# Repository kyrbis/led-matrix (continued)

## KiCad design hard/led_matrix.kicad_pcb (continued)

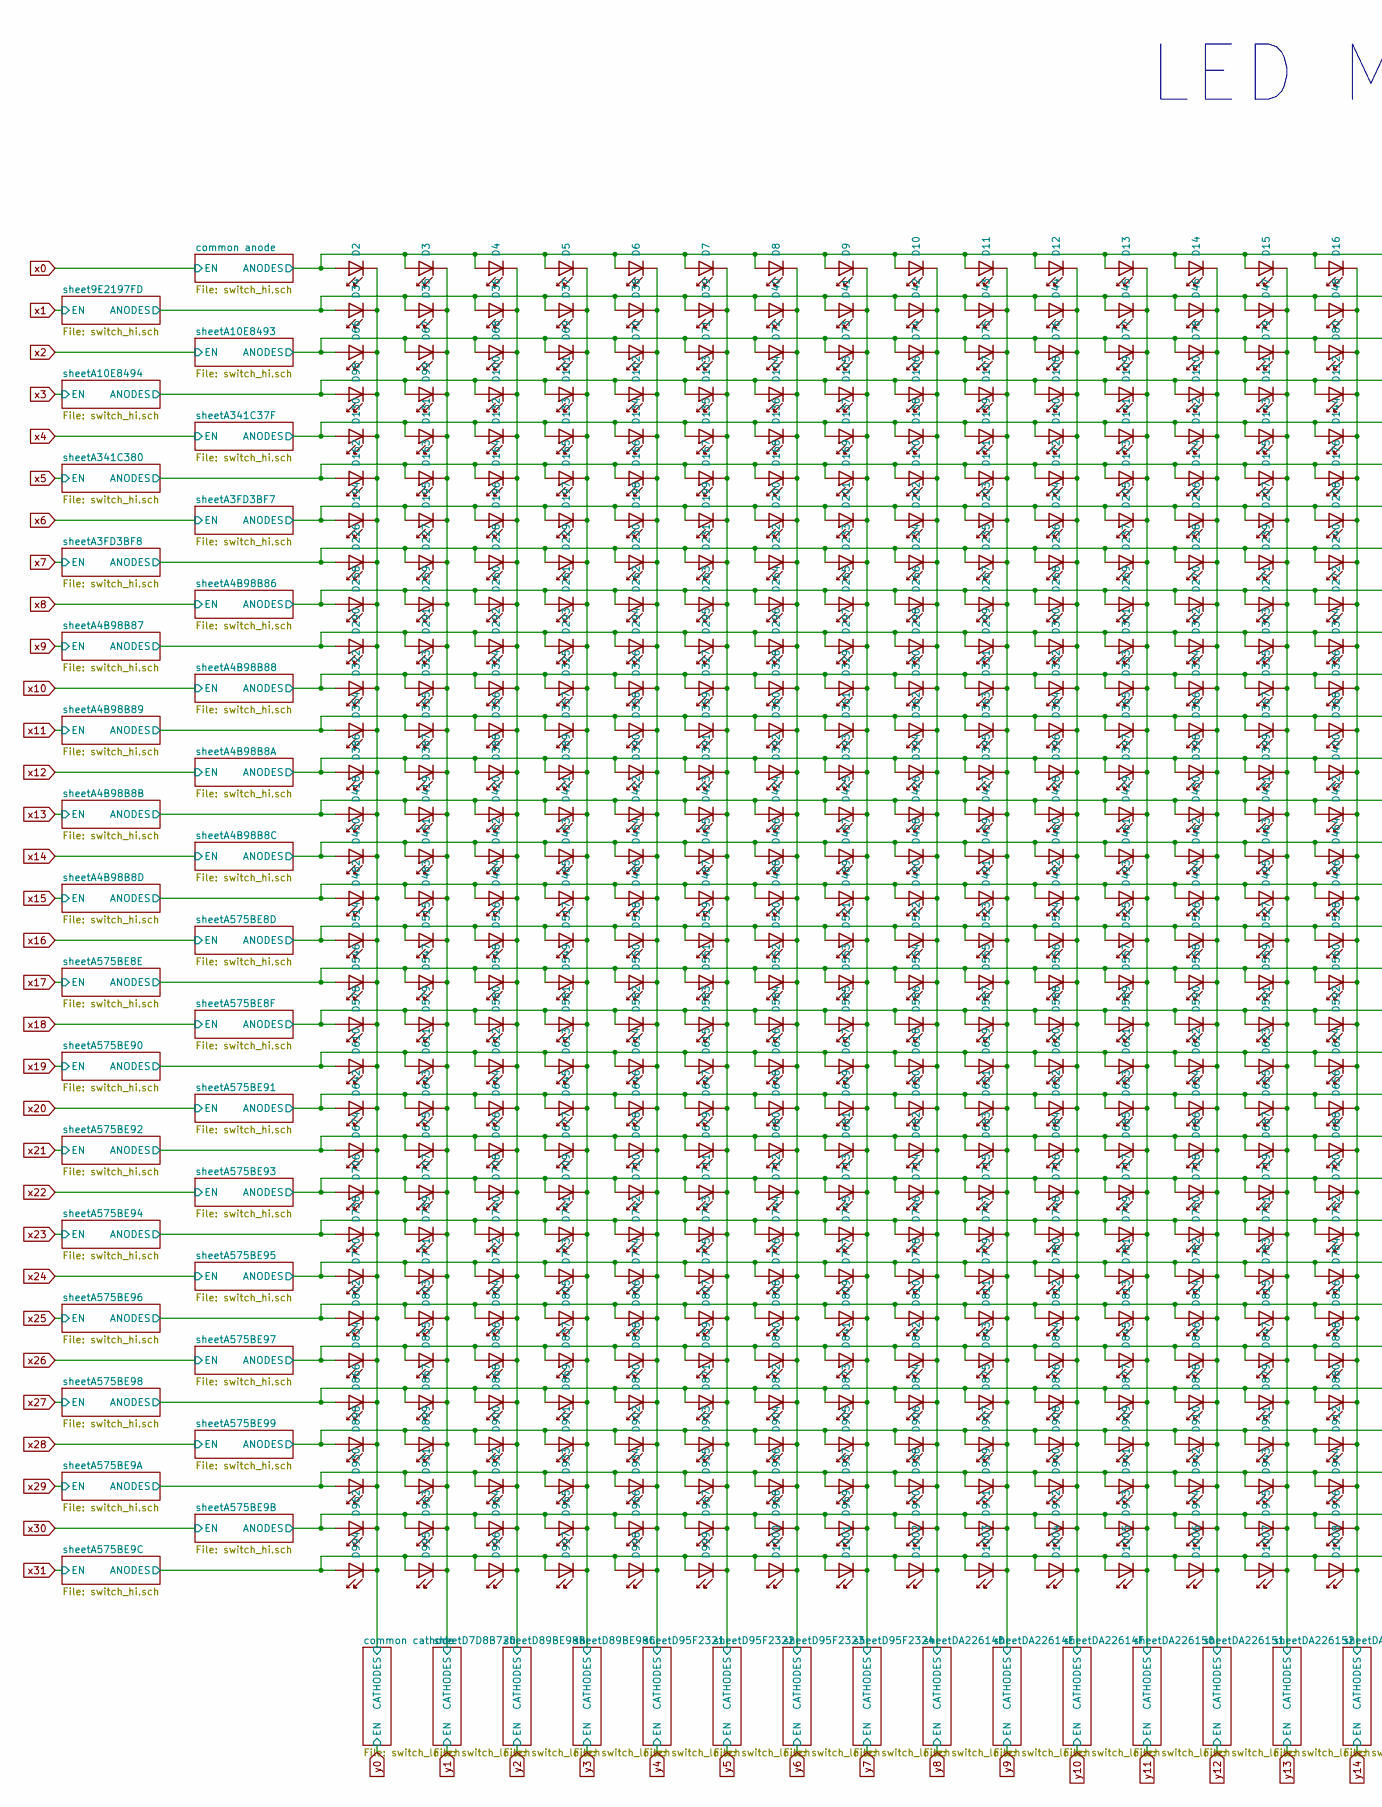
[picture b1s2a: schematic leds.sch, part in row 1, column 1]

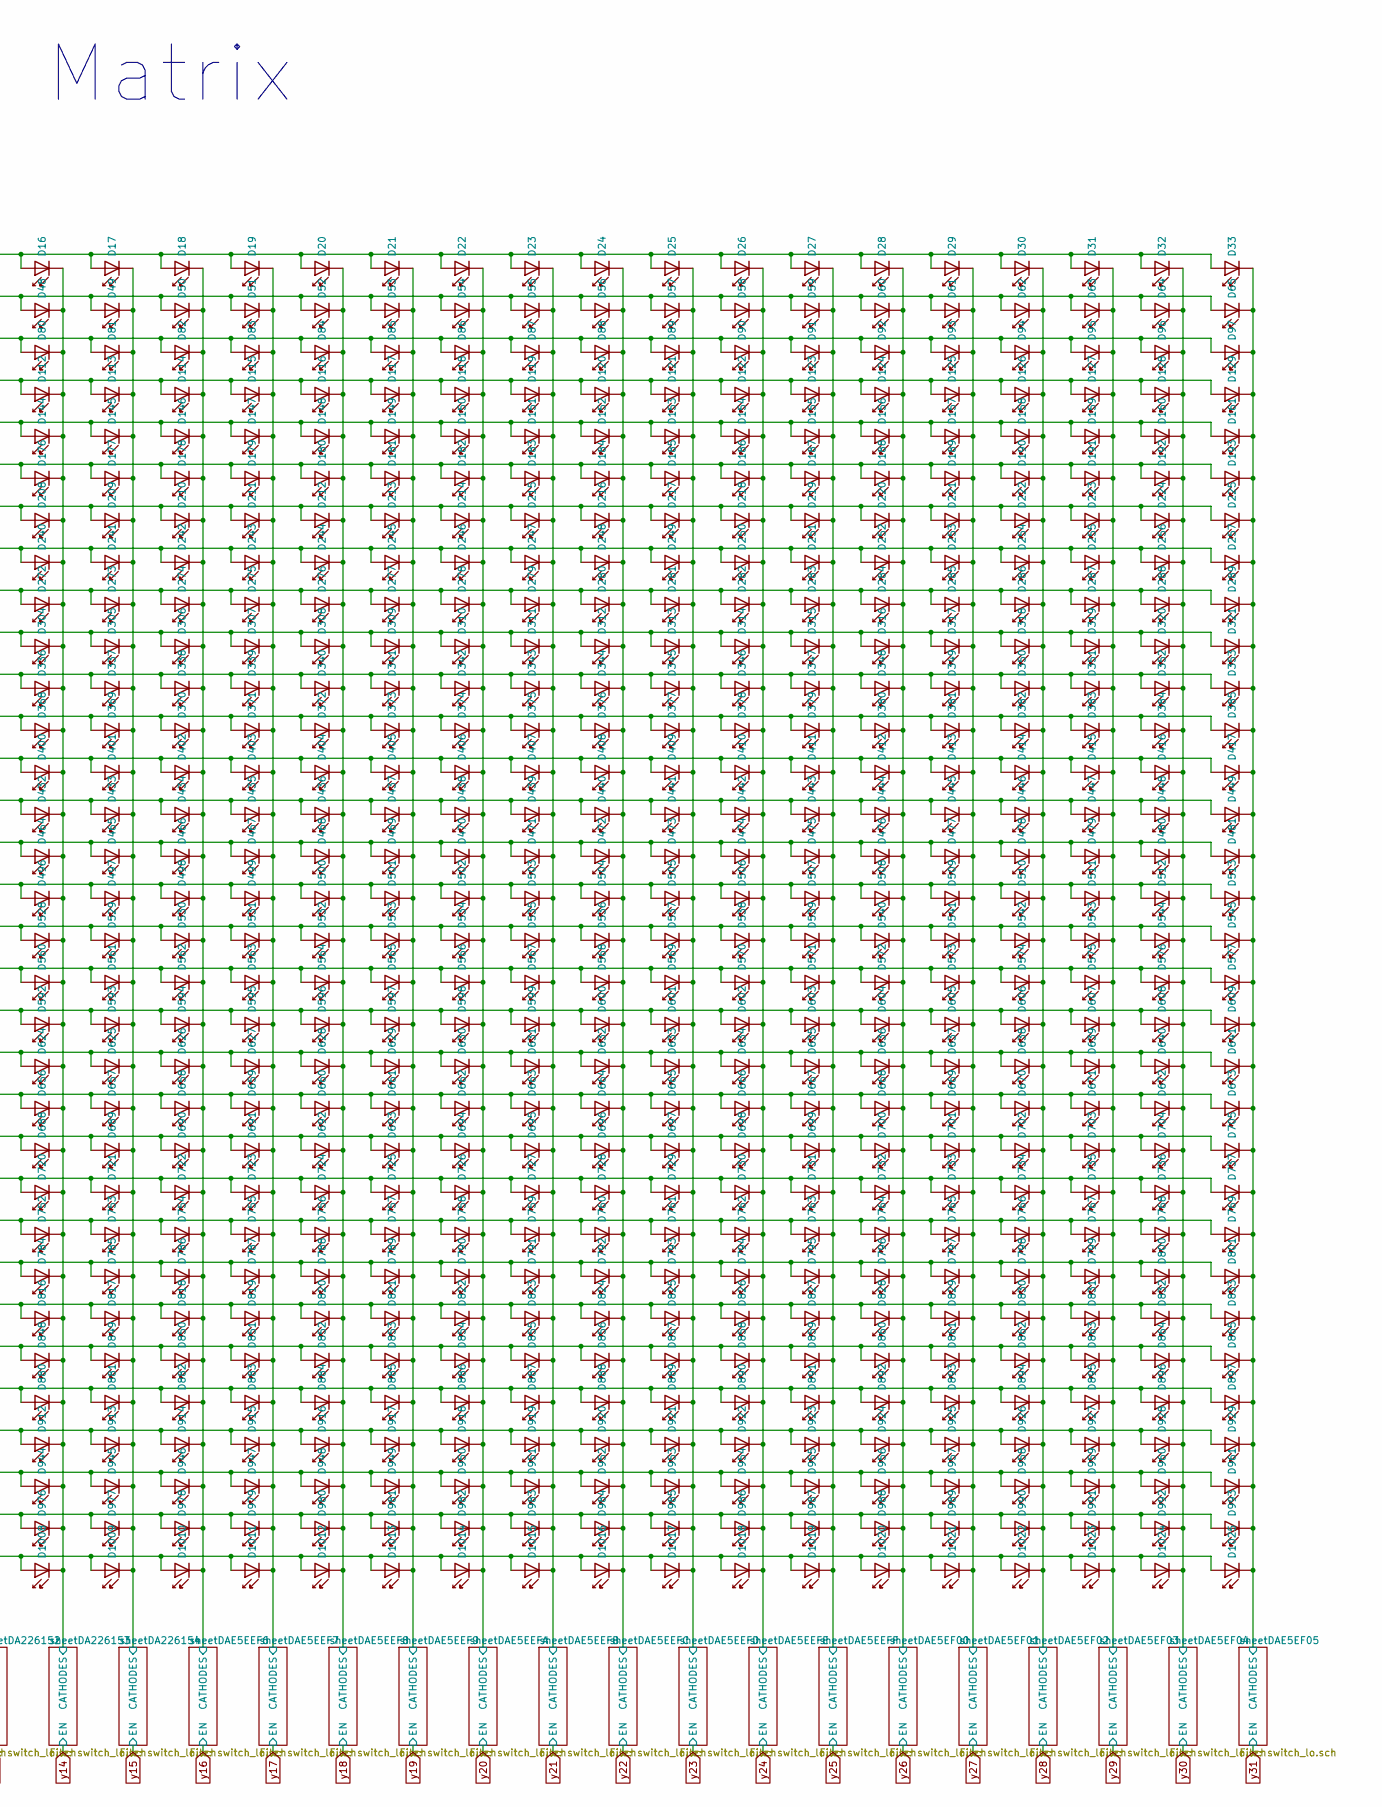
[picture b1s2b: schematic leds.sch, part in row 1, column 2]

Parts:
D2, D3, D4, D5, D6, D7, D8, D9, D10, D11, D12, D13, D14, D15, D16, D17, D18, D19, D20, D21, D22, D23, D24, D25, D26, D27, D28, D29, D30, D31, D32, D33, D34, D35, D36, D37, D38, D39, D40, D41, D42, D43, D44, D45, D46, D47, D48, D49, D50, D51, D52, D53, D54, D55, D56, D57, D58, D59, D60, D61, D62, D63, D64, D65, D66, D67, D68, D69, D70, D71, D72, D73, D74, D75, D76, D77, D78, D79, D80, D81, D82, D83, D84, D85, D86, D87, D88, D89, D90, D91, D92, D93, D94, D95, D96, D97, D98, D99, D100, D101, D102, D103, D104, D105, D106, D107, D108, D109, D110, D111, D112, D113, D114, D115, D116, D117, D118, D119, D120, D121, D122, D123, D124, D125, D126, D127, D128, D129, D130, D131, D132, D133, D134, D135, D136, D137, D138, D139, D140, D141, D142, D143, D144, D145, D146, D147, D148, D149, D150, D151, D152, D153, D154, D155, D156, D157, D158, D159, D160, D161, D162, D163, D164, D165, D166, D167, D168, D169, D170, D171, D172, D173, D174, D175, D176, D177, D178, D179, D180, D181, D182, D183, D184, D185, D186, D187, D188, D189, D190, D191, D192, D193, D194, D195, D196, D197, D198, D199, D200, D201, D202, D203, D204, D205, D206, D207, D208, D209, D210, D211, D212, D213, D214, D215, D216, D217, D218, D219, D220, D221, D222, D223, D224, D225, D226, D227, D228, D229, D230, D231, D232, D233, D234, D235, D236, D237, D238, D239, D240, D241, D242, D243, D244, D245, D246, D247, D248, D249, D250, D251, D252, D253, D254, D255, D256, D257, D258, D259, D260, D261, D262, D263, D264, D265, D266, D267, D268, D269, D270, D271, D272, D273, D274, D275, D276, D277, D278, D279, D280, D281, D282, D283, D284, D285, D286, D287, D288, D289, D290, D291, D292, D293, D294, D295, D296, D297, D298, D299, D300, D301, D302, D303, D304, D305, D306, D307, D308, D309, D310, D311, D312, D313, D314, D315, D316, D317, D318, D319, D320, D321, D322, D323, D324, D325, D326, D327, D328, D329, D330, D331, D332, D333, D334, D335, D336, D337, D338, D339, D340, D341, D342, D343, D344, D345, D346, D347, D348, D349, D350, D351, D352, D353, D354, D355, D356, D357, D358, D359, D360, D361, D362, D363, D364, D365, D366, D367, D368, D369, D370, D371, D372, D373, D374, D375, D376, D377, D378, D379, D380, D381, D382, D383, D384, D385, D386, D387, D388, D389, D390, D391, D392, D393, D394, D395, D396, D397, D398, D399, D400, D401, D402, D403, D404, D405, D406, D407, D408, D409, D410, D411, D412, D413, D414, D415, D416, D417, D418, D419, D420, D421, D422, D423, D424, D425, D426, D427, D428, D429, D430, D431, D432, D433, D434, D435, D436, D437, D438, D439, D440, D441, D442, D443, D444, D445, D446, D447, D448, D449, D450, D451, D452, D453, D454, D455, D456, D457, D458, D459, D460, D461, D462, D463, D464, D465, D466, D467, D468, D469, D470, D471, D472, D473, D474, D475, D476, D477, D478, D479, D480, D481, D482, D483, D484, D485, D486, D487, D488, D489, D490, D491, D492, D493, D494, D495, D496, D497, D498, D499, D500, D501, D502, D503, D504, D505, D506, D507, D508, D509, D510, D511, D512, D513, D514, D515, D516, D517, D518, D519, D520, D521, D522, D523, D524, D525, D526, D527, D528, D529, D530, D531, D532, D533, D534, D535, D536, D537, D538, D539, D540, D541, D542, D543, D544, D545, D546, D547, D548, D549, D550, D551, D552, D553, D554, D555, D556, D557, D558, D559, D560, D561, D562, D563, D564, D565, D566, D567, D568, D569, D570, D571, D572, D573, D574, D575, D576, D577, D578, D579, D580, D581, D582, D583, D584, D585, D586, D587, D588, D589, D590, D591, D592, D593, D594, D595, D596, D597, D598, D599, D600, D601, D602, D603, D604, D605, D606, D607, D608, D609, D610, D611, D612, D613, D614, D615, D616, D617, D618, D619, D620, D621, D622, D623, D624, D625, D626, D627, D628, D629, D630, D631, D632, D633, D634, D635, D636, D637, D638, D639, D640, D641, D642, D643, D644, D645, D646, D647, D648, D649, D650, D651, D652, D653, D654, D655, D656, D657, D658, D659, D660, D661, D662, D663, D664, D665, D666, D667, D668, D669, D670, D671, D672, D673, D674, D675, D676, D677, D678, D679, D680, D681, D682, D683, D684, D685, D686, D687, D688, D689, D690, D691, D692, D693, D694, D695, D696, D697, D698, D699, D700, D701, D702, D703, D704, D705, D706, D707, D708, D709, D710, D711, D712, D713, D714, D715, D716, D717, D718, D719, D720, D721, D722, D723, D724, D725, D726, D727, D728, D729, D730, D731, D732, D733, D734, D735, D736, D737, D738, D739, D740, D741, D742, D743, D744, D745, D746, D747, D748, D749, D750, D751, D752, D753, D754, D755, D756, D757, D758, D759, D760, D761, D762, D763, D764, D765, D766, D767, D768, D769, D770, D771, D772, D773, D774, D775, D776, D777, D778, D779, D780, D781, D782, D783, D784, D785, D786, D787, D788, D789, D790, D791, D792, D793, D794, D795, D796, D797, D798, D799, D800, D801, D802, D803, D804, D805, D806, D807, D808, D809, D810, D811, D812, D813, D814, D815, D816, D817, D818, D819, D820, D821, D822, D823, D824, D825, D826, D827, D828, D829, D830, D831, D832, D833, D834, D835, D836, D837, D838, D839, D840, D841, D842, D843, D844, D845, D846, D847, D848, D849, D850, D851, D852, D853, D854, D855, D856, D857, D858, D859, D860, D861, D862, D863, D864, D865, D866, D867, D868, D869, D870, D871, D872, D873, D874, D875, D876, D877, D878, D879, D880, D881, D882, D883, D884, D885, D886, D887, D888, D889, D890, D891, D892, D893, D894, D895, D896, D897, D898, D899, D900, D901, D902, D903, D904, D905, D906, D907, D908, D909, D910, D911, D912, D913, D914, D915, D916, D917, D918, D919, D920, D921, D922, D923, D924, D925, D926, D927, D928, D929, D930, D931, D932, D933, D934, D935, D936, D937, D938, D939, D940, D941, D942, D943, D944, D945, D946, D947, D948, D949, D950, D951, D952, D953, D954, D955, D956, D957, D958, D959, D960, D961, D962, D963, D964, D965, D966, D967, D968, D969, D970, D971, D972, D973, D974, D975, D976, D977, D978, D979, D980, D981, D982, D983, D984, D985, D986, D987, D988, D989, D990, D991, D992, D993, D994, D995, D996, D997, D998, D999, D1000, D1001, D1002, D1003, D1004, D1005, D1006, D1007, D1008, D1009, D1010, D1011, D1012, D1013, D1014, D1015, D1016, D1017, D1018, D1019, D1020, D1021, D1022, D1023, D1024, D1025: LTST-S270TBKT; LED_LiteOn_LTST-S270TBKT; Mouser_Part_Number 859-LTST-S270TBKT; DigiKey_Part_Number LTST-S270TBKT-5A-ND

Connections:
/led matrix/common anode/ANODES: D2.A, D3.A, D4.A, D5.A, D6.A, D7.A, D8.A, D9.A, D10.A, D11.A, D12.A, D13.A, D14.A, D15.A, D16.A, D17.A, D18.A, D19.A, D20.A, D21.A, D22.A, D23.A, D24.A, D25.A, D26.A, D27.A, D28.A, D29.A, D30.A, D31.A, D32.A, D33.A; also elsewhere on the board
/led matrix/common cathode/CATHODES: D2.C, D34.C, D66.C, D98.C, D130.C, D162.C, D194.C, D226.C, D258.C, D290.C, D322.C, D354.C, D386.C, D418.C, D450.C, D482.C, D514.C, D546.C, D578.C, D610.C, D642.C, D674.C, D706.C, D738.C, D770.C, D802.C, D834.C, D866.C, D898.C, D930.C, D962.C, D994.C; also elsewhere on the board
/led matrix/sheet9E2197FD/ANODES: D34.A, D35.A, D36.A, D37.A, D38.A, D39.A, D40.A, D41.A, D42.A, D43.A, D44.A, D45.A, D46.A, D47.A, D48.A, D49.A, D50.A, D51.A, D52.A, D53.A, D54.A, D55.A, D56.A, D57.A, D58.A, D59.A, D60.A, D61.A, D62.A, D63.A, D64.A, D65.A; also elsewhere on the board
/led matrix/sheetA3FD3BF7/ANODES: D194.A, D195.A, D196.A, D197.A, D198.A, D199.A, D200.A, D201.A, D202.A, D203.A, D204.A, D205.A, D206.A, D207.A, D208.A, D209.A, D210.A, D211.A, D212.A, D213.A, D214.A, D215.A, D216.A, D217.A, D218.A, D219.A, D220.A, D221.A, D222.A, D223.A, D224.A, D225.A; also elsewhere on the board
/led matrix/sheetA3FD3BF8/ANODES: D226.A, D227.A, D228.A, D229.A, D230.A, D231.A, D232.A, D233.A, D234.A, D235.A, D236.A, D237.A, D238.A, D239.A, D240.A, D241.A, D242.A, D243.A, D244.A, D245.A, D246.A, D247.A, D248.A, D249.A, D250.A, D251.A, D252.A, D253.A, D254.A, D255.A, D256.A, D257.A; also elsewhere on the board
/led matrix/sheetA4B98B8A/ANODES: D386.A, D387.A, D388.A, D389.A, D390.A, D391.A, D392.A, D393.A, D394.A, D395.A, D396.A, D397.A, D398.A, D399.A, D400.A, D401.A, D402.A, D403.A, D404.A, D405.A, D406.A, D407.A, D408.A, D409.A, D410.A, D411.A, D412.A, D413.A, D414.A, D415.A, D416.A, D417.A; also elsewhere on the board
/led matrix/sheetA4B98B8B/ANODES: D418.A, D419.A, D420.A, D421.A, D422.A, D423.A, D424.A, D425.A, D426.A, D427.A, D428.A, D429.A, D430.A, D431.A, D432.A, D433.A, D434.A, D435.A, D436.A, D437.A, D438.A, D439.A, D440.A, D441.A, D442.A, D443.A, D444.A, D445.A, D446.A, D447.A, D448.A, D449.A; also elsewhere on the board
/led matrix/sheetA4B98B8C/ANODES: D450.A, D451.A, D452.A, D453.A, D454.A, D455.A, D456.A, D457.A, D458.A, D459.A, D460.A, D461.A, D462.A, D463.A, D464.A, D465.A, D466.A, D467.A, D468.A, D469.A, D470.A, D471.A, D472.A, D473.A, D474.A, D475.A, D476.A, D477.A, D478.A, D479.A, D480.A, D481.A; also elsewhere on the board
/led matrix/sheetA4B98B8D/ANODES: D482.A, D483.A, D484.A, D485.A, D486.A, D487.A, D488.A, D489.A, D490.A, D491.A, D492.A, D493.A, D494.A, D495.A, D496.A, D497.A, D498.A, D499.A, D500.A, D501.A, D502.A, D503.A, D504.A, D505.A, D506.A, D507.A, D508.A, D509.A, D510.A, D511.A, D512.A, D513.A; also elsewhere on the board
/led matrix/sheetA4B98B86/ANODES: D258.A, D259.A, D260.A, D261.A, D262.A, D263.A, D264.A, D265.A, D266.A, D267.A, D268.A, D269.A, D270.A, D271.A, D272.A, D273.A, D274.A, D275.A, D276.A, D277.A, D278.A, D279.A, D280.A, D281.A, D282.A, D283.A, D284.A, D285.A, D286.A, D287.A, D288.A, D289.A; also elsewhere on the board
/led matrix/sheetA4B98B87/ANODES: D290.A, D291.A, D292.A, D293.A, D294.A, D295.A, D296.A, D297.A, D298.A, D299.A, D300.A, D301.A, D302.A, D303.A, D304.A, D305.A, D306.A, D307.A, D308.A, D309.A, D310.A, D311.A, D312.A, D313.A, D314.A, D315.A, D316.A, D317.A, D318.A, D319.A, D320.A, D321.A; also elsewhere on the board
/led matrix/sheetA4B98B88/ANODES: D322.A, D323.A, D324.A, D325.A, D326.A, D327.A, D328.A, D329.A, D330.A, D331.A, D332.A, D333.A, D334.A, D335.A, D336.A, D337.A, D338.A, D339.A, D340.A, D341.A, D342.A, D343.A, D344.A, D345.A, D346.A, D347.A, D348.A, D349.A, D350.A, D351.A, D352.A, D353.A; also elsewhere on the board
/led matrix/sheetA4B98B89/ANODES: D354.A, D355.A, D356.A, D357.A, D358.A, D359.A, D360.A, D361.A, D362.A, D363.A, D364.A, D365.A, D366.A, D367.A, D368.A, D369.A, D370.A, D371.A, D372.A, D373.A, D374.A, D375.A, D376.A, D377.A, D378.A, D379.A, D380.A, D381.A, D382.A, D383.A, D384.A, D385.A; also elsewhere on the board
/led matrix/sheetA10E8493/ANODES: D66.A, D67.A, D68.A, D69.A, D70.A, D71.A, D72.A, D73.A, D74.A, D75.A, D76.A, D77.A, D78.A, D79.A, D80.A, D81.A, D82.A, D83.A, D84.A, D85.A, D86.A, D87.A, D88.A, D89.A, D90.A, D91.A, D92.A, D93.A, D94.A, D95.A, D96.A, D97.A; also elsewhere on the board
/led matrix/sheetA10E8494/ANODES: D98.A, D99.A, D100.A, D101.A, D102.A, D103.A, D104.A, D105.A, D106.A, D107.A, D108.A, D109.A, D110.A, D111.A, D112.A, D113.A, D114.A, D115.A, D116.A, D117.A, D118.A, D119.A, D120.A, D121.A, D122.A, D123.A, D124.A, D125.A, D126.A, D127.A, D128.A, D129.A; also elsewhere on the board
/led matrix/sheetA341C37F/ANODES: D130.A, D131.A, D132.A, D133.A, D134.A, D135.A, D136.A, D137.A, D138.A, D139.A, D140.A, D141.A, D142.A, D143.A, D144.A, D145.A, D146.A, D147.A, D148.A, D149.A, D150.A, D151.A, D152.A, D153.A, D154.A, D155.A, D156.A, D157.A, D158.A, D159.A, D160.A, D161.A; also elsewhere on the board
/led matrix/sheetA341C380/ANODES: D162.A, D163.A, D164.A, D165.A, D166.A, D167.A, D168.A, D169.A, D170.A, D171.A, D172.A, D173.A, D174.A, D175.A, D176.A, D177.A, D178.A, D179.A, D180.A, D181.A, D182.A, D183.A, D184.A, D185.A, D186.A, D187.A, D188.A, D189.A, D190.A, D191.A, D192.A, D193.A; also elsewhere on the board
/led matrix/sheetA575BE8D/ANODES: D514.A, D515.A, D516.A, D517.A, D518.A, D519.A, D520.A, D521.A, D522.A, D523.A, D524.A, D525.A, D526.A, D527.A, D528.A, D529.A, D530.A, D531.A, D532.A, D533.A, D534.A, D535.A, D536.A, D537.A, D538.A, D539.A, D540.A, D541.A, D542.A, D543.A, D544.A, D545.A; also elsewhere on the board
/led matrix/sheetA575BE8E/ANODES: D546.A, D547.A, D548.A, D549.A, D550.A, D551.A, D552.A, D553.A, D554.A, D555.A, D556.A, D557.A, D558.A, D559.A, D560.A, D561.A, D562.A, D563.A, D564.A, D565.A, D566.A, D567.A, D568.A, D569.A, D570.A, D571.A, D572.A, D573.A, D574.A, D575.A, D576.A, D577.A; also elsewhere on the board
/led matrix/sheetA575BE8F/ANODES: D578.A, D579.A, D580.A, D581.A, D582.A, D583.A, D584.A, D585.A, D586.A, D587.A, D588.A, D589.A, D590.A, D591.A, D592.A, D593.A, D594.A, D595.A, D596.A, D597.A, D598.A, D599.A, D600.A, D601.A, D602.A, D603.A, D604.A, D605.A, D606.A, D607.A, D608.A, D609.A; also elsewhere on the board
/led matrix/sheetA575BE9A/ANODES: D930.A, D931.A, D932.A, D933.A, D934.A, D935.A, D936.A, D937.A, D938.A, D939.A, D940.A, D941.A, D942.A, D943.A, D944.A, D945.A, D946.A, D947.A, D948.A, D949.A, D950.A, D951.A, D952.A, D953.A, D954.A, D955.A, D956.A, D957.A, D958.A, D959.A, D960.A, D961.A; also elsewhere on the board
/led matrix/sheetA575BE9B/ANODES: D962.A, D963.A, D964.A, D965.A, D966.A, D967.A, D968.A, D969.A, D970.A, D971.A, D972.A, D973.A, D974.A, D975.A, D976.A, D977.A, D978.A, D979.A, D980.A, D981.A, D982.A, D983.A, D984.A, D985.A, D986.A, D987.A, D988.A, D989.A, D990.A, D991.A, D992.A, D993.A; also elsewhere on the board
/led matrix/sheetA575BE9C/ANODES: D994.A, D995.A, D996.A, D997.A, D998.A, D999.A, D1000.A, D1001.A, D1002.A, D1003.A, D1004.A, D1005.A, D1006.A, D1007.A, D1008.A, D1009.A, D1010.A, D1011.A, D1012.A, D1013.A, D1014.A, D1015.A, D1016.A, D1017.A, D1018.A, D1019.A, D1020.A, D1021.A, D1022.A, D1023.A, D1024.A, D1025.A; also elsewhere on the board
/led matrix/sheetA575BE90/ANODES: D610.A, D611.A, D612.A, D613.A, D614.A, D615.A, D616.A, D617.A, D618.A, D619.A, D620.A, D621.A, D622.A, D623.A, D624.A, D625.A, D626.A, D627.A, D628.A, D629.A, D630.A, D631.A, D632.A, D633.A, D634.A, D635.A, D636.A, D637.A, D638.A, D639.A, D640.A, D641.A; also elsewhere on the board
/led matrix/sheetA575BE91/ANODES: D642.A, D643.A, D644.A, D645.A, D646.A, D647.A, D648.A, D649.A, D650.A, D651.A, D652.A, D653.A, D654.A, D655.A, D656.A, D657.A, D658.A, D659.A, D660.A, D661.A, D662.A, D663.A, D664.A, D665.A, D666.A, D667.A, D668.A, D669.A, D670.A, D671.A, D672.A, D673.A; also elsewhere on the board
/led matrix/sheetA575BE92/ANODES: D674.A, D675.A, D676.A, D677.A, D678.A, D679.A, D680.A, D681.A, D682.A, D683.A, D684.A, D685.A, D686.A, D687.A, D688.A, D689.A, D690.A, D691.A, D692.A, D693.A, D694.A, D695.A, D696.A, D697.A, D698.A, D699.A, D700.A, D701.A, D702.A, D703.A, D704.A, D705.A; also elsewhere on the board
/led matrix/sheetA575BE93/ANODES: D706.A, D707.A, D708.A, D709.A, D710.A, D711.A, D712.A, D713.A, D714.A, D715.A, D716.A, D717.A, D718.A, D719.A, D720.A, D721.A, D722.A, D723.A, D724.A, D725.A, D726.A, D727.A, D728.A, D729.A, D730.A, D731.A, D732.A, D733.A, D734.A, D735.A, D736.A, D737.A; also elsewhere on the board
/led matrix/sheetA575BE94/ANODES: D738.A, D739.A, D740.A, D741.A, D742.A, D743.A, D744.A, D745.A, D746.A, D747.A, D748.A, D749.A, D750.A, D751.A, D752.A, D753.A, D754.A, D755.A, D756.A, D757.A, D758.A, D759.A, D760.A, D761.A, D762.A, D763.A, D764.A, D765.A, D766.A, D767.A, D768.A, D769.A; also elsewhere on the board
/led matrix/sheetA575BE95/ANODES: D770.A, D771.A, D772.A, D773.A, D774.A, D775.A, D776.A, D777.A, D778.A, D779.A, D780.A, D781.A, D782.A, D783.A, D784.A, D785.A, D786.A, D787.A, D788.A, D789.A, D790.A, D791.A, D792.A, D793.A, D794.A, D795.A, D796.A, D797.A, D798.A, D799.A, D800.A, D801.A; also elsewhere on the board
/led matrix/sheetA575BE96/ANODES: D802.A, D803.A, D804.A, D805.A, D806.A, D807.A, D808.A, D809.A, D810.A, D811.A, D812.A, D813.A, D814.A, D815.A, D816.A, D817.A, D818.A, D819.A, D820.A, D821.A, D822.A, D823.A, D824.A, D825.A, D826.A, D827.A, D828.A, D829.A, D830.A, D831.A, D832.A, D833.A; also elsewhere on the board
/led matrix/sheetA575BE97/ANODES: D834.A, D835.A, D836.A, D837.A, D838.A, D839.A, D840.A, D841.A, D842.A, D843.A, D844.A, D845.A, D846.A, D847.A, D848.A, D849.A, D850.A, D851.A, D852.A, D853.A, D854.A, D855.A, D856.A, D857.A, D858.A, D859.A, D860.A, D861.A, D862.A, D863.A, D864.A, D865.A; also elsewhere on the board
/led matrix/sheetA575BE98/ANODES: D866.A, D867.A, D868.A, D869.A, D870.A, D871.A, D872.A, D873.A, D874.A, D875.A, D876.A, D877.A, D878.A, D879.A, D880.A, D881.A, D882.A, D883.A, D884.A, D885.A, D886.A, D887.A, D888.A, D889.A, D890.A, D891.A, D892.A, D893.A, D894.A, D895.A, D896.A, D897.A; also elsewhere on the board
/led matrix/sheetA575BE99/ANODES: D898.A, D899.A, D900.A, D901.A, D902.A, D903.A, D904.A, D905.A, D906.A, D907.A, D908.A, D909.A, D910.A, D911.A, D912.A, D913.A, D914.A, D915.A, D916.A, D917.A, D918.A, D919.A, D920.A, D921.A, D922.A, D923.A, D924.A, D925.A, D926.A, D927.A, D928.A, D929.A; also elsewhere on the board
/led matrix/sheetD7D8B720/CATHODES: D3.C, D35.C, D67.C, D99.C, D131.C, D163.C, D195.C, D227.C, D259.C, D291.C, D323.C, D355.C, D387.C, D419.C, D451.C, D483.C, D515.C, D547.C, D579.C, D611.C, D643.C, D675.C, D707.C, D739.C, D771.C, D803.C, D835.C, D867.C, D899.C, D931.C, D963.C, D995.C; also elsewhere on the board
/led matrix/sheetD89BE98B/CATHODES: D4.C, D36.C, D68.C, D100.C, D132.C, D164.C, D196.C, D228.C, D260.C, D292.C, D324.C, D356.C, D388.C, D420.C, D452.C, D484.C, D516.C, D548.C, D580.C, D612.C, D644.C, D676.C, D708.C, D740.C, D772.C, D804.C, D836.C, D868.C, D900.C, D932.C, D964.C, D996.C; also elsewhere on the board
/led matrix/sheetD89BE98C/CATHODES: D5.C, D37.C, D69.C, D101.C, D133.C, D165.C, D197.C, D229.C, D261.C, D293.C, D325.C, D357.C, D389.C, D421.C, D453.C, D485.C, D517.C, D549.C, D581.C, D613.C, D645.C, D677.C, D709.C, D741.C, D773.C, D805.C, D837.C, D869.C, D901.C, D933.C, D965.C, D997.C; also elsewhere on the board
/led matrix/sheetD95F2321/CATHODES: D6.C, D38.C, D70.C, D102.C, D134.C, D166.C, D198.C, D230.C, D262.C, D294.C, D326.C, D358.C, D390.C, D422.C, D454.C, D486.C, D518.C, D550.C, D582.C, D614.C, D646.C, D678.C, D710.C, D742.C, D774.C, D806.C, D838.C, D870.C, D902.C, D934.C, D966.C, D998.C; also elsewhere on the board
/led matrix/sheetD95F2322/CATHODES: D7.C, D39.C, D71.C, D103.C, D135.C, D167.C, D199.C, D231.C, D263.C, D295.C, D327.C, D359.C, D391.C, D423.C, D455.C, D487.C, D519.C, D551.C, D583.C, D615.C, D647.C, D679.C, D711.C, D743.C, D775.C, D807.C, D839.C, D871.C, D903.C, D935.C, D967.C, D999.C; also elsewhere on the board
/led matrix/sheetD95F2323/CATHODES: D8.C, D40.C, D72.C, D104.C, D136.C, D168.C, D200.C, D232.C, D264.C, D296.C, D328.C, D360.C, D392.C, D424.C, D456.C, D488.C, D520.C, D552.C, D584.C, D616.C, D648.C, D680.C, D712.C, D744.C, D776.C, D808.C, D840.C, D872.C, D904.C, D936.C, D968.C, D1000.C; also elsewhere on the board
/led matrix/sheetD95F2324/CATHODES: D9.C, D41.C, D73.C, D105.C, D137.C, D169.C, D201.C, D233.C, D265.C, D297.C, D329.C, D361.C, D393.C, D425.C, D457.C, D489.C, D521.C, D553.C, D585.C, D617.C, D649.C, D681.C, D713.C, D745.C, D777.C, D809.C, D841.C, D873.C, D905.C, D937.C, D969.C, D1001.C; also elsewhere on the board
/led matrix/sheetDA22614D/CATHODES: D10.C, D42.C, D74.C, D106.C, D138.C, D170.C, D202.C, D234.C, D266.C, D298.C, D330.C, D362.C, D394.C, D426.C, D458.C, D490.C, D522.C, D554.C, D586.C, D618.C, D650.C, D682.C, D714.C, D746.C, D778.C, D810.C, D842.C, D874.C, D906.C, D938.C, D970.C, D1002.C; also elsewhere on the board
/led matrix/sheetDA22614E/CATHODES: D11.C, D43.C, D75.C, D107.C, D139.C, D171.C, D203.C, D235.C, D267.C, D299.C, D331.C, D363.C, D395.C, D427.C, D459.C, D491.C, D523.C, D555.C, D587.C, D619.C, D651.C, D683.C, D715.C, D747.C, D779.C, D811.C, D843.C, D875.C, D907.C, D939.C, D971.C, D1003.C; also elsewhere on the board
/led matrix/sheetDA22614F/CATHODES: D12.C, D44.C, D76.C, D108.C, D140.C, D172.C, D204.C, D236.C, D268.C, D300.C, D332.C, D364.C, D396.C, D428.C, D460.C, D492.C, D524.C, D556.C, D588.C, D620.C, D652.C, D684.C, D716.C, D748.C, D780.C, D812.C, D844.C, D876.C, D908.C, D940.C, D972.C, D1004.C; also elsewhere on the board
/led matrix/sheetDA226150/CATHODES: D13.C, D45.C, D77.C, D109.C, D141.C, D173.C, D205.C, D237.C, D269.C, D301.C, D333.C, D365.C, D397.C, D429.C, D461.C, D493.C, D525.C, D557.C, D589.C, D621.C, D653.C, D685.C, D717.C, D749.C, D781.C, D813.C, D845.C, D877.C, D909.C, D941.C, D973.C, D1005.C; also elsewhere on the board
/led matrix/sheetDA226151/CATHODES: D14.C, D46.C, D78.C, D110.C, D142.C, D174.C, D206.C, D238.C, D270.C, D302.C, D334.C, D366.C, D398.C, D430.C, D462.C, D494.C, D526.C, D558.C, D590.C, D622.C, D654.C, D686.C, D718.C, D750.C, D782.C, D814.C, D846.C, D878.C, D910.C, D942.C, D974.C, D1006.C; also elsewhere on the board
/led matrix/sheetDA226152/CATHODES: D15.C, D47.C, D79.C, D111.C, D143.C, D175.C, D207.C, D239.C, D271.C, D303.C, D335.C, D367.C, D399.C, D431.C, D463.C, D495.C, D527.C, D559.C, D591.C, D623.C, D655.C, D687.C, D719.C, D751.C, D783.C, D815.C, D847.C, D879.C, D911.C, D943.C, D975.C, D1007.C; also elsewhere on the board
/led matrix/sheetDA226153/CATHODES: D16.C, D48.C, D80.C, D112.C, D144.C, D176.C, D208.C, D240.C, D272.C, D304.C, D336.C, D368.C, D400.C, D432.C, D464.C, D496.C, D528.C, D560.C, D592.C, D624.C, D656.C, D688.C, D720.C, D752.C, D784.C, D816.C, D848.C, D880.C, D912.C, D944.C, D976.C, D1008.C; also elsewhere on the board
/led matrix/sheetDA226154/CATHODES: D17.C, D49.C, D81.C, D113.C, D145.C, D177.C, D209.C, D241.C, D273.C, D305.C, D337.C, D369.C, D401.C, D433.C, D465.C, D497.C, D529.C, D561.C, D593.C, D625.C, D657.C, D689.C, D721.C, D753.C, D785.C, D817.C, D849.C, D881.C, D913.C, D945.C, D977.C, D1009.C; also elsewhere on the board
/led matrix/sheetDAE5EEF6/CATHODES: D18.C, D50.C, D82.C, D114.C, D146.C, D178.C, D210.C, D242.C, D274.C, D306.C, D338.C, D370.C, D402.C, D434.C, D466.C, D498.C, D530.C, D562.C, D594.C, D626.C, D658.C, D690.C, D722.C, D754.C, D786.C, D818.C, D850.C, D882.C, D914.C, D946.C, D978.C, D1010.C; also elsewhere on the board
/led matrix/sheetDAE5EEF7/CATHODES: D19.C, D51.C, D83.C, D115.C, D147.C, D179.C, D211.C, D243.C, D275.C, D307.C, D339.C, D371.C, D403.C, D435.C, D467.C, D499.C, D531.C, D563.C, D595.C, D627.C, D659.C, D691.C, D723.C, D755.C, D787.C, D819.C, D851.C, D883.C, D915.C, D947.C, D979.C, D1011.C; also elsewhere on the board
/led matrix/sheetDAE5EEF8/CATHODES: D20.C, D52.C, D84.C, D116.C, D148.C, D180.C, D212.C, D244.C, D276.C, D308.C, D340.C, D372.C, D404.C, D436.C, D468.C, D500.C, D532.C, D564.C, D596.C, D628.C, D660.C, D692.C, D724.C, D756.C, D788.C, D820.C, D852.C, D884.C, D916.C, D948.C, D980.C, D1012.C; also elsewhere on the board
/led matrix/sheetDAE5EEF9/CATHODES: D21.C, D53.C, D85.C, D117.C, D149.C, D181.C, D213.C, D245.C, D277.C, D309.C, D341.C, D373.C, D405.C, D437.C, D469.C, D501.C, D533.C, D565.C, D597.C, D629.C, D661.C, D693.C, D725.C, D757.C, D789.C, D821.C, D853.C, D885.C, D917.C, D949.C, D981.C, D1013.C; also elsewhere on the board
/led matrix/sheetDAE5EEFA/CATHODES: D22.C, D54.C, D86.C, D118.C, D150.C, D182.C, D214.C, D246.C, D278.C, D310.C, D342.C, D374.C, D406.C, D438.C, D470.C, D502.C, D534.C, D566.C, D598.C, D630.C, D662.C, D694.C, D726.C, D758.C, D790.C, D822.C, D854.C, D886.C, D918.C, D950.C, D982.C, D1014.C; also elsewhere on the board
/led matrix/sheetDAE5EEFB/CATHODES: D23.C, D55.C, D87.C, D119.C, D151.C, D183.C, D215.C, D247.C, D279.C, D311.C, D343.C, D375.C, D407.C, D439.C, D471.C, D503.C, D535.C, D567.C, D599.C, D631.C, D663.C, D695.C, D727.C, D759.C, D791.C, D823.C, D855.C, D887.C, D919.C, D951.C, D983.C, D1015.C; also elsewhere on the board
/led matrix/sheetDAE5EEFC/CATHODES: D24.C, D56.C, D88.C, D120.C, D152.C, D184.C, D216.C, D248.C, D280.C, D312.C, D344.C, D376.C, D408.C, D440.C, D472.C, D504.C, D536.C, D568.C, D600.C, D632.C, D664.C, D696.C, D728.C, D760.C, D792.C, D824.C, D856.C, D888.C, D920.C, D952.C, D984.C, D1016.C; also elsewhere on the board
/led matrix/sheetDAE5EEFD/CATHODES: D25.C, D57.C, D89.C, D121.C, D153.C, D185.C, D217.C, D249.C, D281.C, D313.C, D345.C, D377.C, D409.C, D441.C, D473.C, D505.C, D537.C, D569.C, D601.C, D633.C, D665.C, D697.C, D729.C, D761.C, D793.C, D825.C, D857.C, D889.C, D921.C, D953.C, D985.C, D1017.C; also elsewhere on the board
/led matrix/sheetDAE5EEFE/CATHODES: D26.C, D58.C, D90.C, D122.C, D154.C, D186.C, D218.C, D250.C, D282.C, D314.C, D346.C, D378.C, D410.C, D442.C, D474.C, D506.C, D538.C, D570.C, D602.C, D634.C, D666.C, D698.C, D730.C, D762.C, D794.C, D826.C, D858.C, D890.C, D922.C, D954.C, D986.C, D1018.C; also elsewhere on the board
/led matrix/sheetDAE5EEFF/CATHODES: D27.C, D59.C, D91.C, D123.C, D155.C, D187.C, D219.C, D251.C, D283.C, D315.C, D347.C, D379.C, D411.C, D443.C, D475.C, D507.C, D539.C, D571.C, D603.C, D635.C, D667.C, D699.C, D731.C, D763.C, D795.C, D827.C, D859.C, D891.C, D923.C, D955.C, D987.C, D1019.C; also elsewhere on the board
/led matrix/sheetDAE5EF00/CATHODES: D28.C, D60.C, D92.C, D124.C, D156.C, D188.C, D220.C, D252.C, D284.C, D316.C, D348.C, D380.C, D412.C, D444.C, D476.C, D508.C, D540.C, D572.C, D604.C, D636.C, D668.C, D700.C, D732.C, D764.C, D796.C, D828.C, D860.C, D892.C, D924.C, D956.C, D988.C, D1020.C; also elsewhere on the board
/led matrix/sheetDAE5EF01/CATHODES: D29.C, D61.C, D93.C, D125.C, D157.C, D189.C, D221.C, D253.C, D285.C, D317.C, D349.C, D381.C, D413.C, D445.C, D477.C, D509.C, D541.C, D573.C, D605.C, D637.C, D669.C, D701.C, D733.C, D765.C, D797.C, D829.C, D861.C, D893.C, D925.C, D957.C, D989.C, D1021.C; also elsewhere on the board
/led matrix/sheetDAE5EF02/CATHODES: D30.C, D62.C, D94.C, D126.C, D158.C, D190.C, D222.C, D254.C, D286.C, D318.C, D350.C, D382.C, D414.C, D446.C, D478.C, D510.C, D542.C, D574.C, D606.C, D638.C, D670.C, D702.C, D734.C, D766.C, D798.C, D830.C, D862.C, D894.C, D926.C, D958.C, D990.C, D1022.C; also elsewhere on the board
/led matrix/sheetDAE5EF03/CATHODES: D31.C, D63.C, D95.C, D127.C, D159.C, D191.C, D223.C, D255.C, D287.C, D319.C, D351.C, D383.C, D415.C, D447.C, D479.C, D511.C, D543.C, D575.C, D607.C, D639.C, D671.C, D703.C, D735.C, D767.C, D799.C, D831.C, D863.C, D895.C, D927.C, D959.C, D991.C, D1023.C; also elsewhere on the board
/led matrix/sheetDAE5EF04/CATHODES: D32.C, D64.C, D96.C, D128.C, D160.C, D192.C, D224.C, D256.C, D288.C, D320.C, D352.C, D384.C, D416.C, D448.C, D480.C, D512.C, D544.C, D576.C, D608.C, D640.C, D672.C, D704.C, D736.C, D768.C, D800.C, D832.C, D864.C, D896.C, D928.C, D960.C, D992.C, D1024.C; also elsewhere on the board
/led matrix/sheetDAE5EF05/CATHODES: D33.C, D65.C, D97.C, D129.C, D161.C, D193.C, D225.C, D257.C, D289.C, D321.C, D353.C, D385.C, D417.C, D449.C, D481.C, D513.C, D545.C, D577.C, D609.C, D641.C, D673.C, D705.C, D737.C, D769.C, D801.C, D833.C, D865.C, D897.C, D929.C, D961.C, D993.C, D1025.C; also elsewhere on the board

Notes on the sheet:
LED Matrix

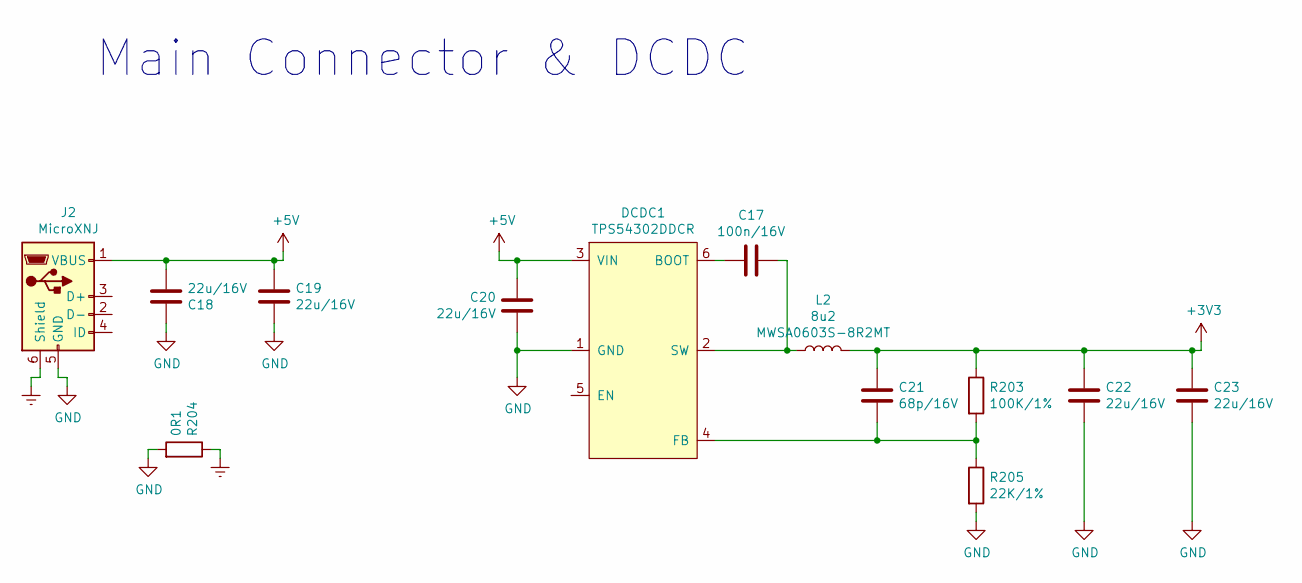
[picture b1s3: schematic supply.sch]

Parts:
C17: 100n/16V; C_0402_1005Metric
C18, C19, C20, C22, C23: 22u/16V; C_0805_2012Metric
C21: 68p/16V; C_0402_1005Metric
DCDC1: TPS54302DDCR; SOT-23-6_Handsoldering; MPN TPS54302DDCR; DigiKey_Part_Number 296-46237-1-ND
J2: MicroXNJ; Connectors_SHOU HAN_MICRO 4P DIP; MPN MICRO 4P DIP; JLCPCB_Part_Number C456008
L2: 8u2; L_Sunking_MWSA0603S; MPN MWSA0603S-8R2MT; JLCPCB_Part_Number C408450
R203: 100K/1%; R_0402_1005Metric
R204: 0R1; R_0805_2012Metric
R205: 22K/1%; R_0402_1005Metric

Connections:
+3V3: C21.2, C22.2, C23.2, L2.2, R203.1; also elsewhere on the board
+5V: C18.1, C19.2, C20.2, DCDC1.3 (VIN), J2.1 (VBUS); also elsewhere on the board
Earth: J2.6 (Shield), R204.1
GND: C18.2, C19.1, C20.1, C22.1, C23.1, DCDC1.1 (GND), J2.5 (GND), R204.2, R205.2; also elsewhere on the board
unnamed: C17.1, DCDC1.2 (SW), L2.1
unnamed: C17.2, DCDC1.6 (BOOT)
unnamed: C21.1, DCDC1.4 (FB), R203.2, R205.1

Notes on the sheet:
Main Connector & DCDC
